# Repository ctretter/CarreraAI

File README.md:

# CarreraAI
Slot car racing ghost car using artificial intelligence algorithms

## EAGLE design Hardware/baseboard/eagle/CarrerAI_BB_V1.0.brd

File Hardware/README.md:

# Deprecated due to power supply issues

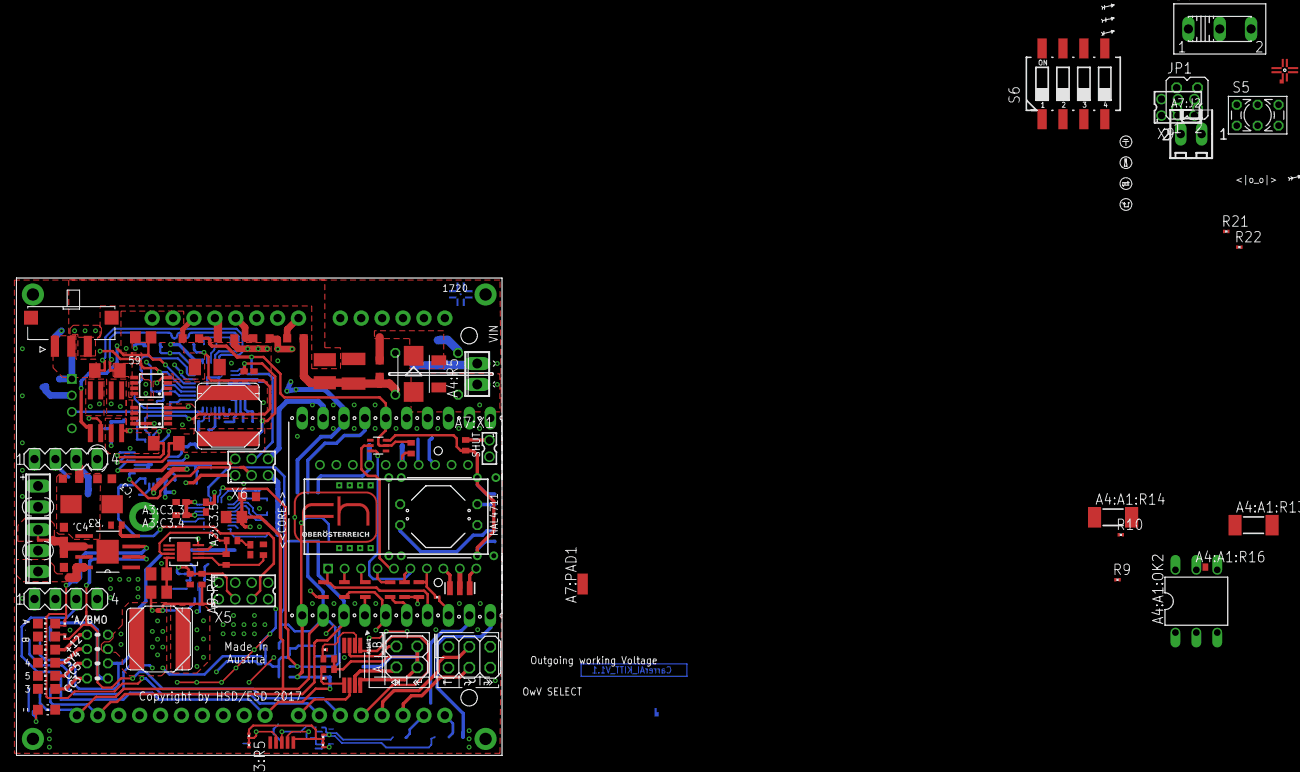
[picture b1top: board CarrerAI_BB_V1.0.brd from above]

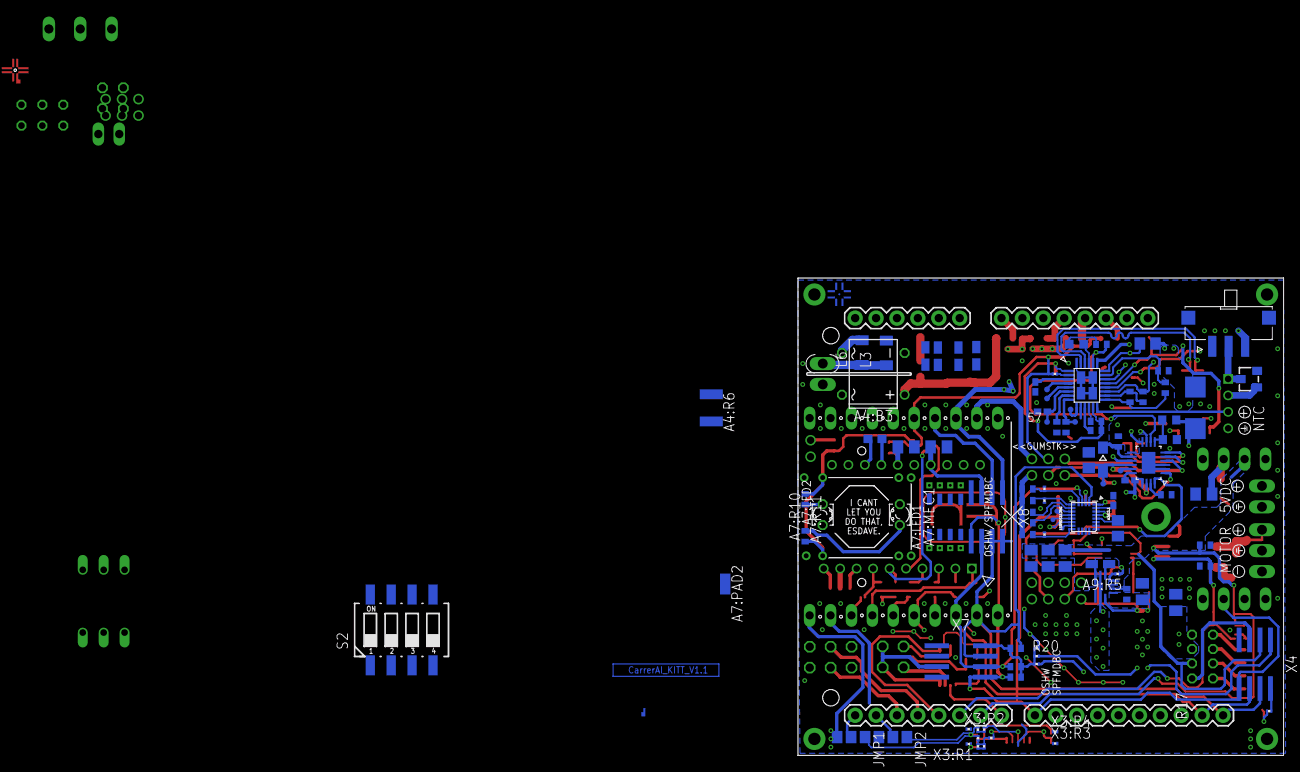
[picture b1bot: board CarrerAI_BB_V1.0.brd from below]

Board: 4 copper layers, 59.0 x 58.0 mm, 227 parts (102 on the bottom side), 139 nets.

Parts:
A2:C1: 4.7uF/25V; C0805K
A2:C2: 100nF/25V⇤; C0603K
A2:C3: 47uF/25V⇤; CT6032
A2:C4, A2:C5: 220nF/25V⇤; C0603
A2:L1, A4:L1: BEAD; L2012C
A2:R1, A2:R2: 10kR/⎑; R0402
A2:R3: 2k2R; R0402
A2:U1: DRV8871; HSOP8
A3:C3.1, A3:C3.XX: 10nF/⇤; C0805
A3:C3.2, A3:C3.3, A3:C3.4, A3:C3.5: 100nF/⇤; C0402K
A3:R3.1, A3:R3.2, A3:R3.5, A3:R3.6, A5:R11, A5:R12, A7:R9: 10kR/⎒; R0402
A3:R3.3, A3:R3.4, A3:R3.11: 10kR/⎑; R0201
A3:R3.9: 60R/⇤; R0603
A3:R3.10: 10k/⎒; R0402
A3:U3.1: LSM9DS1LONG; KITT.IC_LGA-24
A3:☇1, A3:☇2, A3:☇3: PTR1TP06R; TP06R
A4:A1:OK2: Si8710; DIL06
A4:A1:R13, A4:A1:R14: MINI_MELF-0207R
A4:A1:R16: R0402
A4:B3: DBDB102G; DB
A4:C1: 10uF; C1210K
A4:D1: SMB
A4:F1: 1.5A->750mA; R1210
A4:R1, A4:R3: 10kR; R0805W
A4:R2, A4:R4: 2.2kR; R0805W
A4:R5: VARISTORCN1206; CT/CN1206
A4:R6: VARISTORCN1210; CT/CN1210
A5:C1: 47nF/⇤; C0603K
A5:C2: 100uF/~5V; C1206K
A5:C4, A6:C5, A10:C1: 1uF/⇤; C0402K
A5:C5, A5:C6: 10nF/⇤; C0402K
A5:R1: 8.2mR/⚻; R1206-KELV
A5:R2: 16kR/⇤; R0402
A5:R3: 1MR; R0805
A5:R4: 270kR; R0402
A5:R5: 5mR; R0805
A5:R6: 100kR/1%; R0402
A5:R7: 27kR/1%; R0402
A5:R8: 68kR/1%; R0402
A5:R9, A5:R10: 1kR/⇤; R0402
A5:T1: IRF7328; SOIC8
A5:U1: LTC4000LTC4000EUFD-ARMIN; QFN-28_UFD-L_LONG
A5:☇1, A5:☇2, A5:☇3, A5:☇6, A5:☇7, A6:☇1, A6:☇5: PTR1TP07R; TP07R
A6:C1: 1nF/⇤; C0402
A6:C2: 4.7uF/⇤; C0805
A6:C3: 100nF/⇤; C0402
A6:C4: 100uF; C/6032-28R
A6:D1: 30VBD,0.2A; SOD323-W
A6:L1: 10uH; TAIYO-YUDEN.NRS8030T4R7MJGJ
A6:R1: 15mR/25mW⚻; R1206-KELV
A6:R2: 51kR/1%; R0603
A6:R3: 12kR/1%; R0603
A6:T1, A6:T2: XX; MSOP8
A6:U1: LTC3891QFN50P-LONG; QFN50P-LONG
A7:C1: 2.2uF/⇤; C1608
A7:C2, A7:C3: 100nF/⇤; C0805K
A7:DCL1, A7:DCL2: DCL.OSH'3MM-SLK'; DCL.LOGO-OSH.3MM
A7:J2: 22-27-2021-02; 6410-02
A7:LED1, A7:LED2: LZR181
A7:MEC1: MEC.HAL4711/OPTICS; MEC.HAL4711
A7:PAD1, A7:PAD2: SMD1,27-2,54
A7:R1, A7:R5, A7:R6: 10kR/⎒; MINI_MELF-0102R
A7:R2, A7:R3, A7:R4: 100R/⇤; MINI_MELF-0102R
A7:R7, A7:R10, A7:R11: 200R; R0402
A7:R8: 0R; R0201
A7:U1: ADNS-3080
A7:U2: SI1922EDH; SC70-6
A7:X1: 87758-0216
A7:Y1: 24MHz; RESON-SMD
A7:⌁1, A7:⌁2, A7:⌁3, A7:⌁4, A7:⌁5, A7:⌁6, A7:⌁7, A7:⌁8, A7:⌁9, A7:⌁10, A7:⌁11, A7:⌁12, A7:⌁13, A7:⌁14, A7:⌁15, A7:⌁16, A7:⌁17, A7:⌁18, A7:⌁19, A7:⌁20: SINGLEPAD40MIL-BREAK; PAD40MIL.BREAK
A9:C1: 10uF/⇤; C0805K
A9:C2, A9:C3, A9:C4: 22uF/⇤; C0805K
A9:C5: 100nF; C0805K
A9:L1: 1uH; TAIYO-YUDEN.NRS8030T4R7MJGJ
A9:R1: 10kR/⎒; R0805W
A9:R2: 0R/⎵; R0402
A9:R3: 1MR/⎵; R0402
A9:R4: ~10kR/⎵; R0402
A9:R5: R0201
A9:U1: TPS6123X5V-LONG; 9-VQFN-HR_LONG
A10:R1: 430R; R0402
A10:R2: 25kR; R0402
A10:R3, A10:R4: XXMR; M0805
A10:R7: 2.32MR; R0402
A10:REF2: REF.LOGO.UASUAS-GRADE; DCL.LOGO.FHOOE-6MM-S
A10:U1: LTC1540CDD-LONG; DFN-8_DD
A11:U1: 2NANDSOP8; SOP65P490X110-8N
AMO: MOTO; CHIP-LED0805
BMO: MOTO; CHIP-LED0805
D2: MMBZXAL; TO236
JMP1, JMP2: 0R-JUMPA; A0R-JMP
JP1: JP2Q
JP4: 2X02
L1, L2, L4, L5: BEAD/0R/⎵; L2012C
L3, L6: CM CHOKE; L3216C
LED1: VINS; CHIP-LED0805
LED2: DC3; CHIP-LED0805
LED3: DC5; CHIP-LED0805
LED4: SY4; CHIP-LED0805
LED5: PROBLEM; CHIP-LED0805
R1, R8, R15, R16: 100R; 0204V
R2, R6, R7, R9, R10, R11, R12, R18, R19, R20, R21, R22: R0201
R3, R4, R5, R13, R14: 10k/⎒; R0402
R17: 100R; R0201
REF1: REF.EDULIMIT; REF_EAGLE.EDULIMIT
S1, S3: SS312SAH4-R; SW_SS312SAH4-R
S2, S6: 219-04; CTS-219-04
S4: 255SB
S5: 9450-2
SV1, SV2: MA04-1
U$1: PASSER-CIRCLE
X1: JST-4POS-2X4POS; JST-PHR-4
X1.2: TACH/LAP; 2X03
X2: 3POL254
X2.2: VRAILS+; 2POL254
X2.3: SoC; 2POL254
X3:R1, X3:R2, X3:R3, X3:R4, X3:R5, X3:R21, X3:R22, X3:R23, X3:R24, X3:R25, X3:R26, X3:R27, X3:R28, X3:R29: R0201
X3:U$2: 1051330011; POS-5
X4: SYSTEMI-SW; SYSTEWI-BR1.SOIC8C
X5: 87758-0816
X6, X9: 87758-0616
X7: SYSTEMI-SE; SYSTEWI-BR1.SOIC8C
X8: STMI-CW/GPIO; SYSTEWI-BR1.SOIC16
XA1: ARDUINO_UNO; AU_PINS

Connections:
!CS0: A7:R1.2, A7:U1.1, A7:⌁14.P$1, XA1.IO.10
!CS1: A7:R8.2, A7:⌁13.P$1, XA1.IO.9
!RST: A5:U1.2, R2.2
+3V3: A3:C3.3.1, A3:C3.4.1, A3:C3.5.1, A3:R3.1.1, A3:R3.2.1, A3:R3.5.1, A3:R3.6.1, A3:R3.10.1, A3:U3.1.1, A3:U3.1.3, A3:U3.1.22, A3:U3.1.23, A7:C2.1, A7:C3.1, A7:LED1.A, A7:LED2.A, A7:R1.1, A7:R5.1, A7:R6.1, A7:R9.1, A7:U1.12, A7:U1.15, A7:U1.17, A7:X1.2, A7:⌁4.P$1, A11:U1.8, JP4.2, JP4.4, L2.1, R1.2, R6.2, R13.2, R14.2, X1.2.5, X1.2.6, X4.6, X6.5, X6.6, X7.6, X8.6
+4.1V: A5:R8.2, A5:T1.7, A5:T1.8, A5:U1.17, S1.3, SV2.1
+5V: A7:⌁5.P$1, A9:C2.1, A9:C3.1, A9:C4.1, A9:R1.2, A9:U1.6, A9:U1.9, L1.1, R7.2, R15.1, SV2.2, X2.3.2, X3:R23.2, X4.7, X5.2, X8.7
+18V: A2:C1.1, A2:L1.2, A4:B3.+, A4:C1.1, A4:F1.1, A4:L1.2, A4:R3.2, A4:R5.2, L4.1, R8.1, SV2.3
A2:ILIM: A2:R3.1, A2:U1.4
A2:VM: A2:C2.1, A2:C3.+, A2:C4.1, A2:L1.1, A2:U1.5
A3:CS_AG: A3:R3.1.2, A3:U3.1.7
A3:CS_M: A3:R3.2.2, A3:U3.1.8
A3:DEN_AG: A3:R3.10.2, A3:R3.11.1, A3:U3.1.13
A3:DRDY_M: A3:U3.1.9, A3:☇1.TP
A3:INT2_AG: A3:U3.1.12, A3:☇3.TP
A3:INT_M: A3:U3.1.10, A3:☇2.TP
A3:SDO_AG: A3:R3.3.1, A3:R3.6.2, A3:U3.1.5
A3:SDO_M: A3:R3.4.1, A3:R3.5.2, A3:U3.1.6
A3:↔C1: A3:C3.2.1, A3:U3.1.24
A3:↔CAP: A3:C3.1.1, A3:U3.1.21
A4:A1:GND: A4:A1:OK2.4, A4:A1:R14.1
A4:A1:N$1: A4:A1:OK2.5, A4:A1:R13.1, A4:A1:R16.2
A4:A1:N$2: A4:A1:OK2.2, A4:A1:R14.2
A4:A1:N$3: A4:A1:OK2.6, A4:A1:R16.1
A4:N$1: A4:D1.C, A4:L1.1, A4:R1.2
A5:BGATE: A5:T1.2, A5:U1.18
A5:BIAS: A5:C4.1, A5:R11.2, A5:R12.2, A5:U1.1, A5:U1.13
A5:CC: A5:C1.2, A5:U1.25
A5:CL: A5:R9.2, A5:U1.8, A5:☇6.TP
A5:CSN: A5:R5.1, A5:T1.1, A5:U1.19
A5:CX: A5:R10.2, A5:U1.7
A5:IBMON: A5:C6.1, A5:U1.6, A5:☇7.TP
A5:IGATE: A5:R3.2, A5:T1.4, A5:U1.22
A5:IIMON: A5:C5.1, A5:U1.3
A5:IL: A5:U1.4, A5:☇3.TP
A5:N$4: A5:C1.1, A5:R2.1
A5:N$8: A5:R7.1, A5:R8.1, A5:U1.16
A5:OFB: A5:R4.1, A5:R6.2, A5:U1.21
A5:TMR: A5:U1.9, A5:☇1.TP
A5:↔CLN: A5:R1.K+, A5:U1.26
A5:↔FBG: A5:R6.1, A5:R7.2, A5:U1.15
A5:↔IN: A5:R1.K-, A5:U1.27
A6:BG: A6:T2.4, A6:U1.13
A6:DDC.EXTVCC: A6:U1.15, A6:☇1.TP
A6:SW✳: A6:C3.2, A6:L1.2, A6:T1.1, A6:T1.2, A6:T1.3, A6:T2.5, A6:T2.6, A6:T2.7, A6:T2.8, A6:U1.11
A6:TG: A6:T1.4, A6:U1.10
A6:TRACK/SS: A6:C1.1, A6:U1.19
A6:~SENSE+: A6:L1.1, A6:R1.-
A6:↔BOOST: A6:C3.1, A6:D1.C, A6:U1.12
A6:↔ILIM: A6:C2.1, A6:D1.A, A6:U1.14, A6:U1.18, A6:☇5.TP
A6:↔SENSE+: A6:R1.K+, A6:U1.6
A6:↔SENSE-: A6:R1.K-, A6:U1.5
A6:↔VFB: A6:R2.2, A6:R3.1, A6:U1.7
A7:!PD: A7:R6.2, A7:R8.1, A7:U1.7
A7:LEDCTRL: A7:U1.5, A7:U2.2
A7:N$1: A7:LED2.K, A7:R11.2
A7:N$2: A7:LED1.K, A7:R10.2
A7:N$5: A7:C1.1, A7:U1.13
A7:N$6: A7:C1.2, A7:U1.14
A7:OD\!SHUT: A7:R7.1, A7:R10.1, A7:R11.1, A7:U2.6
A7:RST: A7:R5.2, A7:U1.6, A7:U2.3
A7:SHUT: A7:R7.2, A7:X1.1
A7:U1.GUARD: A7:U1.9, A7:Y1.2
A7:U1.MISO: A7:R2.2, A7:U1.2
A7:U1.MOSI: A7:R4.2, A7:U1.4
A7:U1.OSCIN✳: A7:U1.10, A7:Y1.1
A7:U1.OSCOUT✳: A7:U1.8, A7:Y1.3
A7:U1.SCLK: A7:R3.2, A7:U1.3
A9:CC: A9:C5.1, A9:R2.2, A9:U1.4
A9:✳SW: A9:L1.2, A9:U1.2
A10:COMP: A10:C1.1, A10:R1.1
A10:HYST: A10:R2.2, A10:R7.2, A10:U1.5
A10:IN+&REF: A10:R1.2, A10:R2.1, A10:U1.3, A10:U1.6
A10:IN-: A10:R3.2, A10:R4.1, A10:U1.4
AUX.USB/D+_P: JMP2.1, X3:R24.1
AUX.USB/D-_N: JMP1.1, X3:R25.1
DDC.CLN/VIN: A5:R1.+, A6:C5.1, A6:T1.5, A6:T1.6, A6:T1.7, A6:T1.8, A6:U1.17
GND: A2:C1.2, A2:C2.2, A2:C3.-, A2:C5.2, A2:R1.2, A2:R2.2, A2:R3.2, A2:U1.1, A2:U1.7, A2:U1.THERMAL, A3:C3.1.2, A3:C3.2.2, A3:C3.3.2, A3:C3.4.2, A3:C3.5.2, A3:C3.XX.2, A3:R3.3.2, A3:R3.4.2, A3:R3.9.2, A3:R3.11.2, A3:U3.1.14, A3:U3.1.15, A3:U3.1.16, A3:U3.1.17, A3:U3.1.18, A3:U3.1.19, A3:U3.1.20, A4:C1.2, A4:R2.1, A4:R4.1, A4:R5.1, A5:C2.2, A5:C4.2, A5:C5.2, A5:C6.2, A5:R9.1, A5:R10.1, A5:U1.10, A5:U1.28, A5:U1.EP-NE, A5:U1.EP-NW, A5:U1.EP-SE, A5:U1.EP-SW, A6:C1.2, A6:C2.2, A6:C4.-, A6:C5.2, A6:R3.2, A6:T2.1, A6:T2.2, A6:T2.3, A6:U1.2, A6:U1.3, A6:U1.16, A6:U1.21, A7:C2.2, A7:C3.2, A7:U1.16, A7:U1.19, A7:U2.1, A7:U2.4, A7:⌁1.P$1, A7:⌁10.P$1, A9:C1.2, A9:C2.2, A9:C3.2, A9:C4.2, A9:C5.2, A9:R2.1, A9:R3.1, A9:U1.1, A9:U1.5, A10:C1.2, A10:R3.1, A10:R7.1, A10:U1.1, A10:U1.2, A10:U1.EP, A11:U1.4, AMO.C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
ITH: A5:R2.2, A5:U1.24, A6:U1.8
LAP: X1.2.3, XA1.IO.2
MISO: A7:R2.1, A7:⌁16.P$1, XA1.IO.11
MOSI: A7:R4.1, A7:⌁15.P$1, XA1.IO.12
unnamed: A11:U1.3, JP4.1
unnamed: A11:U1.7, JP4.3
unnamed: LED1.A, R8.2
unnamed: L3.1, L6.1, X2.2.2
unnamed: A11:U1.2, R11.2, R13.1
unnamed: A11:U1.5, R12.2, R14.1
unnamed: LED2.A, R1.1
unnamed: LED3.A, R15.2
unnamed: A4:B3.AC1, L6.2
unnamed: LED4.A, R16.1
unnamed: LED5.A, R17.1
unnamed: R17.2, X4.1
unnamed: AMO.A, R18.1
unnamed: BMO.A, R19.1
PWR.MOTA: A2:R2.1, A2:U1.2, R19.2, XA1.IO.5
PWR.MOTB: A2:R1.1, A2:U1.3, R18.2, XA1.IO.6
SCLK: A7:R3.1, A7:⌁17.P$1, XA1.IO.13
SYSTWI.!INT: A3:C3.XX.1, A3:R3.9.1, A3:U3.1.11, A7:⌁20.P$1, R5.1, SV1.3, X4.4, X7.4, X8.4, XA1.IO.8
SYSTWI.SCL: A3:U3.1.2, A7:⌁19.P$1, R3.1, SV1.1, X4.2, X7.2, X8.2, XA1.SCL
SYSTWI.SDA: A3:U3.1.4, A7:⌁18.P$1, R4.1, SV1.2, X4.3, X7.3, X8.3, XA1.SDA
SYSTWI.VBUS: R3.2, R4.2, R5.2, R6.1, R7.1, R20.1, X7.1
TACH: X1.2.4, XA1.IO.3
TOP.5VEN: A9:R3.2, A9:R4.1, A9:R5.1, A9:R5.2, A9:U1.7, A10:U1.8, X5.3
TOP.!CHRG: A5:R11.1, A5:U1.12
TOP.!FLT: A5:R12.1, A5:U1.11
TOP.!RST: A7:R9.2, A7:U2.5, A7:⌁6.P$1, L5.1, R2.1, X6.4
TOP.BAT+NTC: A5:U1.14, X1.3
TOP.BAT/CON: D2.2, S1.2, X1.1
TOP.ENC: A5:U1.5, A5:☇2.TP
TOP.FREQ: A6:U1.20, X5.5
TOP.INACT: A9:R1.1, A9:U1.8
TOP.MODE: A6:U1.1, X6.3
TOP.MOT-: A2:U1.8, X2.1
TOP.MTXS: A7:PAD2.1, A7:⌁12.P$1, JMP2.3
TOP.MVPRW: A4:R3.1, A4:R4.2
TOP.ODA: A11:U1.1, XA1.IO.4
TOP.ODB: A11:U1.6, XA1.IO.7
TOP.OS1IS2: A5:T1.3, A5:U1.23, A6:C4.+, A6:R1.+, A6:R2.1
TOP.PGOOD: A6:U1.9, X6.1
TOP.RRX: A4:R1.1, A4:R2.2, A7:PAD1.1, A7:⌁11.P$1, JMP1.3
TOP.RUN: A6:U1.4, X6.2
UNO.3V3: L2.2, XA1.3.3V
UNO.5V: L1.2, XA1.5V
UNO.RESET: L5.2, XA1.RESET
UNO.RX: JMP1.2, XA1.IO.0
UNO.TX: JMP2.2, XA1.IO.1
UNO.VIN: L4.2, XA1.VIN
VCC/2: A4:B3.AC2, A4:D1.A, A7:⌁7.P$1, X2.2.1
VF+OUT/IPC: A4:F1.2, S3.3
VF+OUT/SWITCH: A5:R1.-, S3.1, S3.2
VSYS: A5:C2.1, A5:R3.1, A5:R4.2, A5:R5.2, A5:T1.5, A5:T1.6, A5:U1.20, A7:⌁3.P$1, A9:C1.1, A9:L1.1, A9:R4.2, A9:U1.3, A10:R4.2, A10:U1.7, R16.2, R20.2, X3:R29.2, X4.8, X5.1, X8.8
X3:B-ID: X3:R5.1, X3:R27.2, X3:U$2.4
X3:N$5: X3:R22.2, X3:R24.2
X3:N$6: X3:R21.2, X3:R25.2, X3:R26.2, X3:R28.2
X3:O>D+: X3:R22.1, X3:U$2.3
X3:O>D-: X3:R21.1, X3:U$2.2
X3:O>VBUS: X3:R23.1, X3:R27.1, X3:R29.1, X3:U$2.1
✳TOP.MOT+: A2:C4.2, A2:C5.1, A2:U1.6, X2.3

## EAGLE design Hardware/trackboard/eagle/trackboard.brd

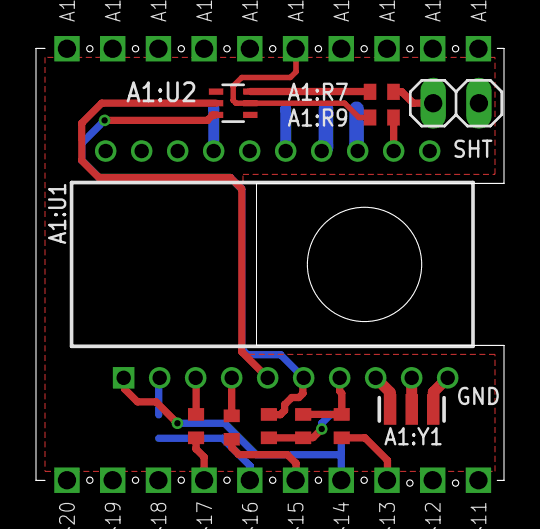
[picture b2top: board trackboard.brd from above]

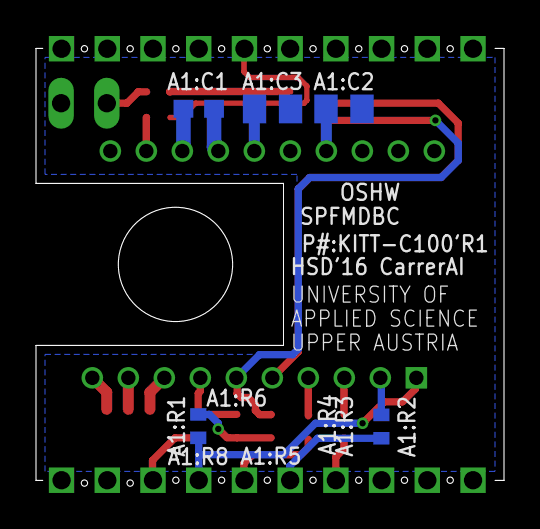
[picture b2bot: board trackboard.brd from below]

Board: 4 copper layers, 26.0 x 24.0 mm, 37 parts (6 on the bottom side), 21 nets.

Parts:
A1:C1: 2.2uF/⇤; C1608
A1:C2, A1:C3: 100nF/⇤; C0805K
A1:DCL2: DCL.OSH'3MM-SLK'; DCL.LOGO-OSH.3MM
A1:J1: 1X02
A1:R1, A1:R5, A1:R6, A1:R9: 10kR/⎒; R0402
A1:R2, A1:R3, A1:R4: 100R/⇤; R0402
A1:R7: 200R; R0402
A1:R8: 0R; R0402
A1:U1: ADNS-3080
A1:U2: SI1922EDH; SC70-6
A1:Y1: 24MHz; RESON-SMD
A1:⌁1, A1:⌁2, A1:⌁3, A1:⌁4, A1:⌁5, A1:⌁6, A1:⌁7, A1:⌁8, A1:⌁9, A1:⌁10, A1:⌁11, A1:⌁12, A1:⌁13, A1:⌁14, A1:⌁15, A1:⌁16, A1:⌁17, A1:⌁18, A1:⌁19, A1:⌁20: SINGLEPAD40MIL; PAD40MIL

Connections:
A1:!CS0: A1:R1.2, A1:U1.1, A1:⌁14.X
A1:!CS1: A1:R8.2, A1:⌁13.X
A1:!PD: A1:R6.2, A1:R8.1, A1:U1.7
A1:!RESET: A1:R9.2, A1:U2.5, A1:⌁6.X
A1:+3V3: A1:C2.1, A1:C3.1, A1:J1.1, A1:R1.1, A1:R5.1, A1:R6.1, A1:R9.1, A1:U1.12, A1:U1.15, A1:U1.17, A1:⌁4.X
A1:GND: A1:C2.2, A1:C3.2, A1:U1.16, A1:U1.19, A1:U2.1, A1:U2.4, A1:⌁1.X, A1:⌁10.X
A1:LEDCTRL: A1:U1.5, A1:U2.2
A1:MISO: A1:R2.1, A1:⌁16.X
A1:MOSI: A1:R4.1, A1:⌁15.X
A1:N$1: A1:R7.1, A1:U2.6
A1:N$5: A1:C1.1, A1:U1.13
A1:N$6: A1:C1.2, A1:U1.14
A1:N$8: A1:J1.2, A1:R7.2
A1:RST: A1:R5.2, A1:U1.6, A1:U2.3
A1:SCLK: A1:R3.1, A1:⌁17.X
A1:U1.GUARD: A1:U1.9, A1:Y1.2
A1:U1.MISO: A1:R2.2, A1:U1.2
A1:U1.MOSI: A1:R4.2, A1:U1.4
A1:U1.OSCIN✳: A1:U1.10, A1:Y1.1
A1:U1.OSCOUT✳: A1:U1.8, A1:Y1.3
A1:U1.SCLK: A1:R3.2, A1:U1.3

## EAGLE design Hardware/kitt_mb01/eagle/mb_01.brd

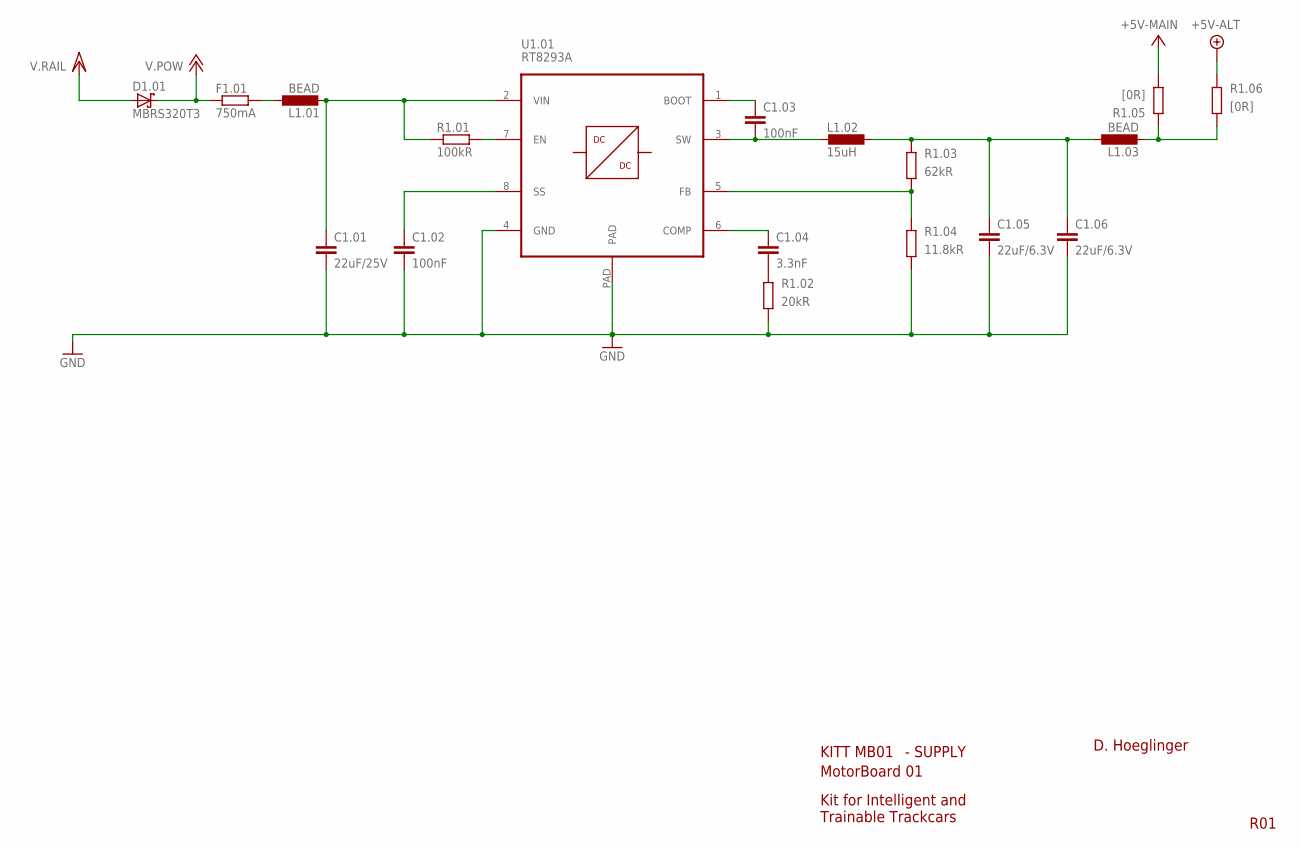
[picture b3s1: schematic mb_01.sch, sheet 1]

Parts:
C1.01: 22uF/25V; C1210K
C1.02, C1.03: 100nF; C0402K
C1.04: 3.3nF; C0402K
C1.05, C1.06: 22uF/6.3V; C1206K
D1.01: MBRS320T3; SMC
F1.01: 750mA; R1210
L1.01, L1.03: BEAD; L4516C
L1.02: 15uH; TAIYO-YUDEN.NRS8030T4R7MJGJ
R1.01: 100kR; R0402
R1.02: 20kR; R0402
R1.03: 62kR; R0402
R1.04: 11.8kR; R0402
R1.05, R1.06: [0R]; R0402
U1.01: RT8293A; SOIC-8-PAD

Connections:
+5V: R1.05.1, R1.06.2; also elsewhere on the board
+12V: D1.01.C, F1.01.1; also elsewhere on the board
GND: C1.01.2, C1.02.2, C1.05.2, C1.06.2, R1.02.1, R1.04.1, U1.01.4 (GND), U1.01.PAD; also elsewhere on the board
unnamed: F1.01.2, L1.01.1
unnamed: C1.01.1, L1.01.2, R1.01.1, U1.01.2 (VIN)
unnamed: R1.01.2, U1.01.7 (EN)
unnamed: C1.02.1, U1.01.8 (SS)
unnamed: C1.04.2, R1.02.2
unnamed: C1.04.1, U1.01.6 (COMP)
unnamed: R1.03.1, R1.04.2, U1.01.5 (FB)
unnamed: C1.05.1, C1.06.1, L1.02.1, L1.03.1, R1.03.2
unnamed: C1.03.2, L1.02.2, U1.01.3 (SW)
unnamed: C1.03.1, U1.01.1 (BOOT)
unnamed: L1.03.2, R1.05.2, R1.06.1
VCC/2: D1.01.A; also elsewhere on the board

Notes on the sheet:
KITT MB01
Kit for Intelligent and Trainable Trackcars
MotorBoard 01
- SUPPLY
D. Hoeglinger
R01

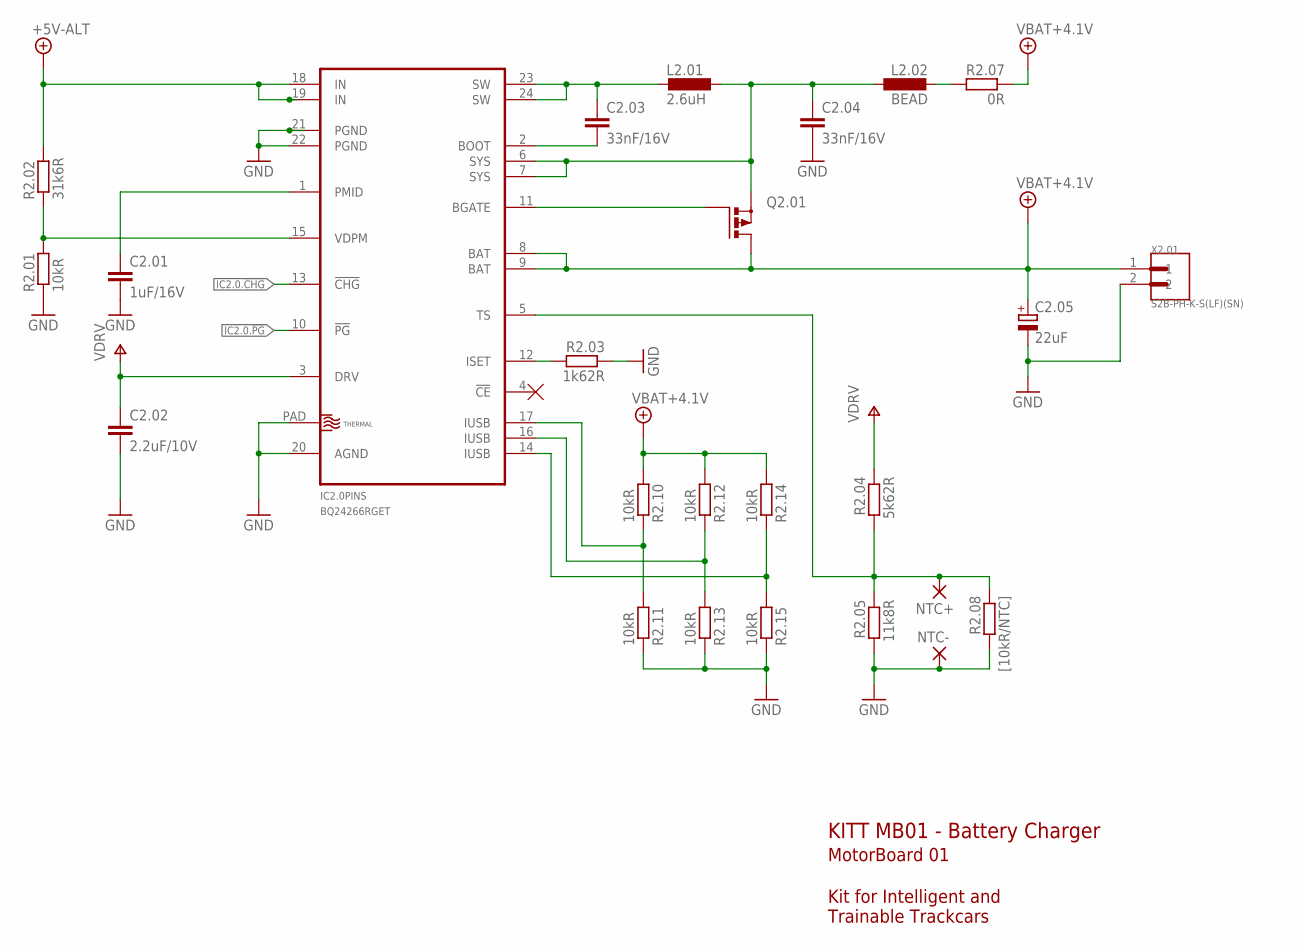
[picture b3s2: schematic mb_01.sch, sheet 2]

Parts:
C2.01: 1uF/16V; C0805
C2.02: 2.2uF/10V; C0603K
C2.03: 33nF/16V; C0603
C2.04: 33nF/16V; C0805
C2.05: 22uF; A/3216-18R
IC2.0: BQ24266RGET; VQFN-24
L2.01: 2.6uH; TAIYO-YUDEN.NRS8030T4R7MJGJ
L2.02: BEAD; L4516C
NTC+: SMD2; SMD1,27-2,54
NTC-: SMD2; SMD1,27-2,54
Q2.01: P-MOSFET-SO8; SO-08
R2.01, R2.10, R2.11, R2.12, R2.13, R2.14, R2.15: 10kR; R0402
R2.02: 31k6R; R0402
R2.03: 1k62R; R0402
R2.04: 5k62R; R0402
R2.05: 11k8R; R0402
R2.07: 0R; R0402
R2.08: [10kR/NTC]; R0402
X2.01: S2B-PH-K-S(LF)(SN); JST_S2B-PH-K-S(LF)(SN)

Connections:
+4.1V: C2.05.+, IC2.0.8 (BAT), IC2.0.9 (BAT), Q2.01.5 (D), Q2.01.6 (D), Q2.01.7 (D), Q2.01.8 (D), R2.07.1, R2.10.2, R2.12.2, R2.14.2, X2.01.1; also elsewhere on the board
+5V: IC2.0.18 (IN), IC2.0.19 (IN), R2.02.2; also elsewhere on the board
GND: C2.01.2, C2.02.2, C2.04.2, C2.05.-, IC2.0.20 (AGND), IC2.0.21 (PGND), IC2.0.22 (PGND), IC2.0.PAD (THERMAL), NTC-.1, R2.01.1, R2.03.1, R2.05.2, R2.08.2, R2.11.1, R2.13.1, R2.15.1, X2.01.2; also elsewhere on the board
unnamed 30: IC2.0.15 (VDPM), R2.01.2, R2.02.1; also elsewhere on the board
unnamed: L2.02.2, R2.07.2
unnamed 33: IC2.0.12 (ISET), R2.03.2; also elsewhere on the board
unnamed 34: IC2.0.17 (IUSB), R2.10.1, R2.11.2; also elsewhere on the board
unnamed 35: IC2.0.16 (IUSB), R2.12.1, R2.13.2; also elsewhere on the board
unnamed 36: IC2.0.14 (IUSB), R2.14.1, R2.15.2; also elsewhere on the board
U2.0/BGATE: IC2.0.11 (BGATE), Q2.01.4 (G); also elsewhere on the board
U2.0/BOOT: C2.03.2, IC2.0.2 (BOOT); also elsewhere on the board
U2.0/DRV: C2.02.1, IC2.0.3 (DRV), R2.04.1; also elsewhere on the board
U2.0/PMID: C2.01.1, IC2.0.1 (PMID); also elsewhere on the board
U2.0/SW: C2.03.1, IC2.0.23 (SW), IC2.0.24 (SW), L2.01.2; also elsewhere on the board
U2.0/SYS: C2.04.1, IC2.0.6 (SYS), IC2.0.7 (SYS), L2.01.1, L2.02.1, Q2.01.1 (S), Q2.01.2 (S), Q2.01.3 (S); also elsewhere on the board
U2.0/TS: IC2.0.5 (TS), NTC+.1, R2.04.2, R2.05.1, R2.08.1; also elsewhere on the board

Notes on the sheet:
KITT MB01 - Battery Charger
Kit for Intelligent and Trainable Trackcars
MotorBoard 01

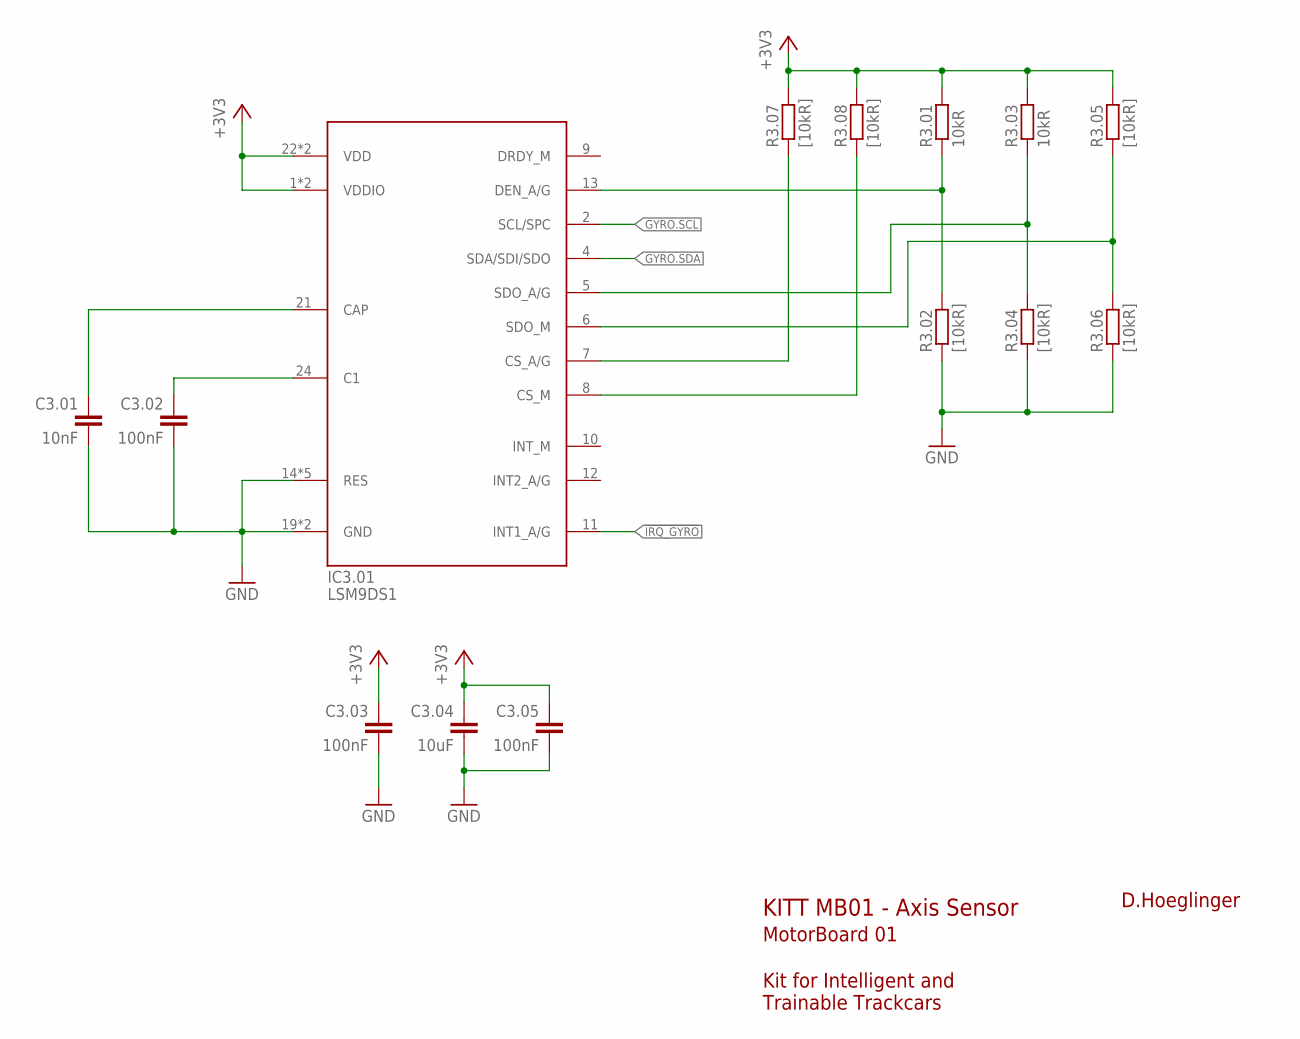
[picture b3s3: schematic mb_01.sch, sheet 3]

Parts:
C3.01: 10nF; C0603
C3.02, C3.03, C3.05: 100nF; C0402
C3.04: 10uF; C0603K
IC3.01: LSM9DS1; LGA-24
R3.01, R3.03: 10kR; R0402
R3.02, R3.04, R3.05, R3.06, R3.07, R3.08: [10kR]; R0402

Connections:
!IRQ_GYRO: IC3.01.11 (INT1_A/G); also elsewhere on the board
+3V3: C3.03.1, C3.04.1, C3.05.1, IC3.01.1 (VDDIO), IC3.01.3 (VDDIO), IC3.01.22 (VDD), IC3.01.23 (VDD), R3.01.2, R3.03.2, R3.05.2, R3.07.2, R3.08.2; also elsewhere on the board
GND: C3.01.2, C3.02.2, C3.03.2, C3.04.2, C3.05.2, IC3.01.14 (RES), IC3.01.15 (RES), IC3.01.16 (RES), IC3.01.17 (RES), IC3.01.18 (RES), IC3.01.19 (GND), IC3.01.20 (GND), R3.02.1, R3.04.1, R3.06.1; also elsewhere on the board
GYRO.SCL: IC3.01.2 (SCL/SPC); also elsewhere on the board
GYRO.SDA: IC3.01.4 (SDA/SDI/SDO); also elsewhere on the board
unnamed: C3.01.1, IC3.01.21 (CAP)
unnamed: C3.02.1, IC3.01.24 (C1)
unnamed: IC3.01.13 (DEN_A/G), R3.01.1, R3.02.2
unnamed: IC3.01.5 (SDO_A/G), R3.03.1, R3.04.2
unnamed: IC3.01.7 (CS_A/G), R3.07.1
unnamed: IC3.01.6 (SDO_M), R3.05.1, R3.06.2
unnamed: IC3.01.8 (CS_M), R3.08.1

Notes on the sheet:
KITT MB01 - Axis Sensor
Kit for Intelligent and Trainable Trackcars
MotorBoard 01
D.Hoeglinger

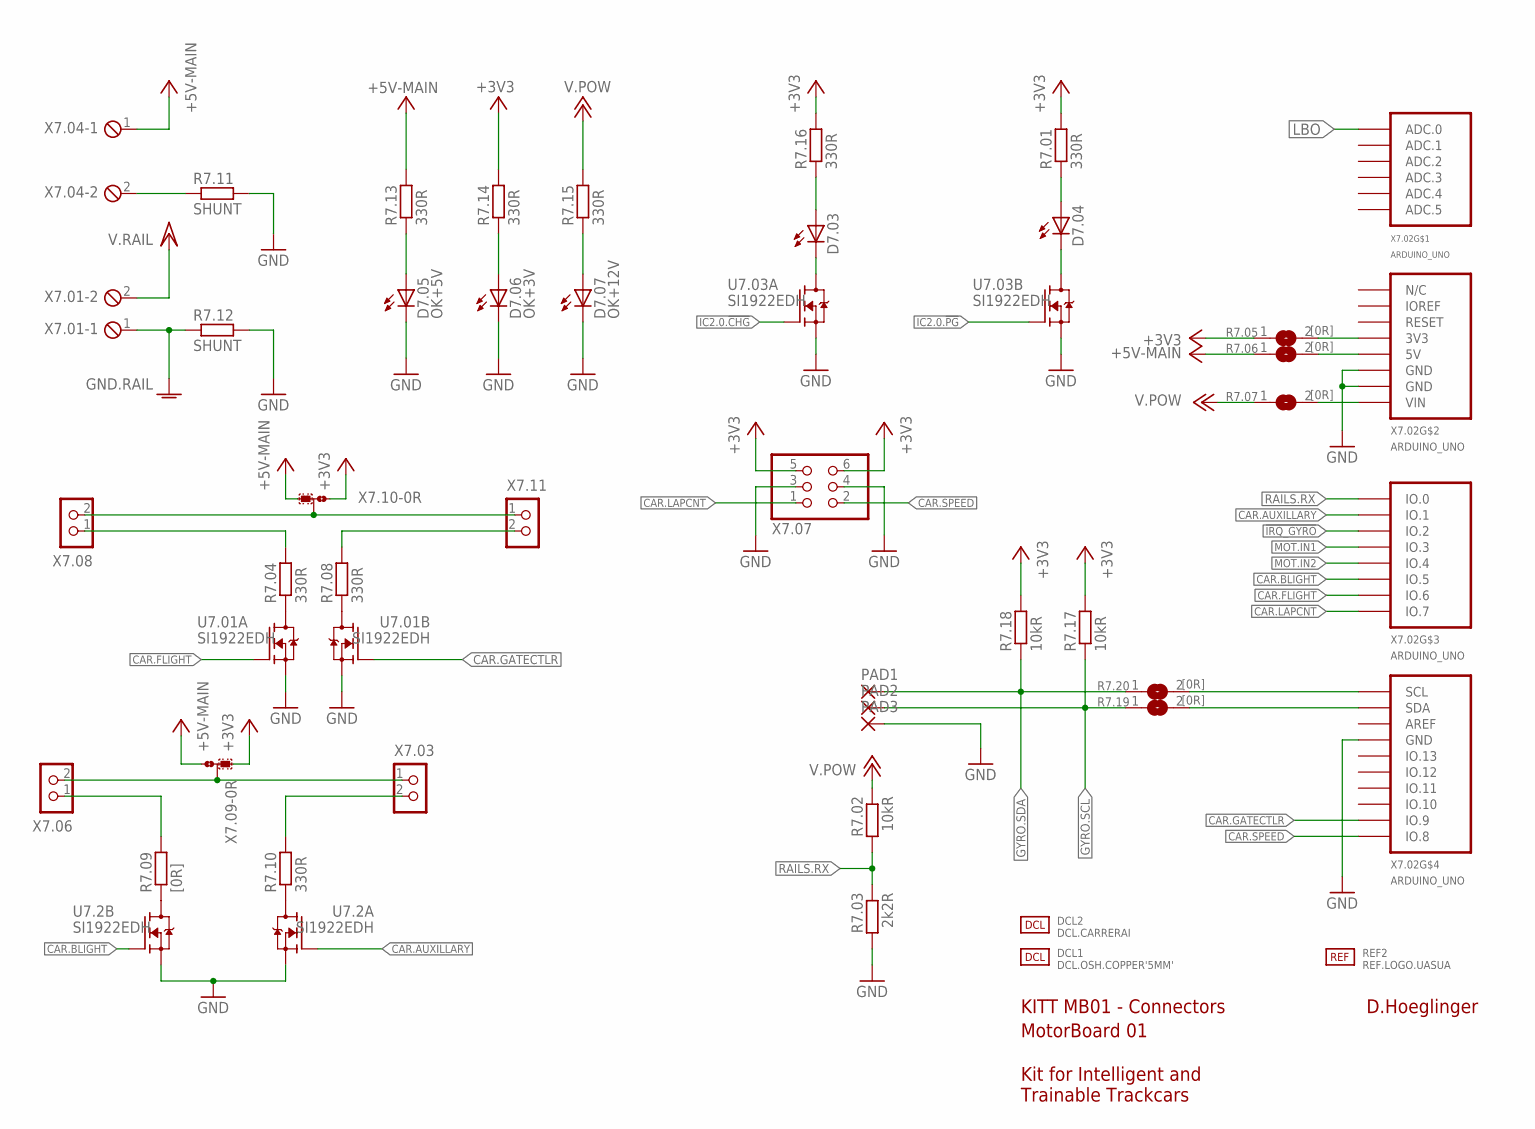
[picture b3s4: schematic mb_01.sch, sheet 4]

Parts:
D7.03, D7.04: LEDCHIPLED_1206; CHIPLED_1206
D7.05: OK+5V; CHIPLED_1206
D7.06: OK+3V; CHIPLED_1206
D7.07: OK+12V; CHIPLED_1206
DCL1: DCL.OSH.COPPER'5MM'; DCL.LOGO-OSH.5MM
DCL2: DCL.CARRERAI; DCL.LOGO-CARRERAI.W30MM
PAD1, PAD2, PAD3: SMD2; SMD1,27-2,54
R7.01, R7.04, R7.08, R7.10, R7.13, R7.14, R7.15, R7.16: 330R; R0603
R7.02: 10kR; M0805
R7.03: 2k2R; M0805
R7.05, R7.06, R7.07, R7.19, R7.20: [0R]; SJ
R7.09: [0R]; R0603
R7.11, R7.12: SHUNT; R1206
R7.17, R7.18: 10kR; R0402
REF2: REF.LOGO.UASUA; REF_LOGO_UASUA
U7.01, U7.2, U7.03: SI1922EDH; SC70-6
X7.01, X7.04: MPT2; 2POL254
X7.02: ARDUINO_UNO; AU_PINS
X7.03, X7.06, X7.08, X7.11: CON_HEADER_1X02; M1X2_MALE_RIGHT_ANGLED_SMD
X7.07: PINHD-2X3/90; 2X03/90
X7.09, X7.10: 0R-JUMPA; A0R-JMP

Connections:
!IRQ_GYRO: X7.02.IO.2; also elsewhere on the board
+3V3: R7.01.2, R7.05.1, R7.14.2, R7.16.2, R7.17.2, R7.18.2, X7.07.5, X7.07.6, X7.09.1, X7.10.1; also elsewhere on the board
+5V: R7.06.1, R7.13.2, X7.04.1, X7.09.3, X7.10.3; also elsewhere on the board
+12V: R7.02.1, R7.07.1, R7.15.2; also elsewhere on the board
CAR.AUXILLARY: U7.2.2 (G), X7.02.IO.1
CAR.BLIGHT: U7.2.5 (G), X7.02.IO.5
CAR.FLIGHT: U7.01.2 (G), X7.02.IO.6
CAR.GATECTLR: U7.01.5 (G), X7.02.IO.9
CAR.LAPCNT: X7.02.IO.7, X7.07.1
CAR.SPEED: X7.02.IO.8, X7.07.2
GND: D7.05.C, D7.06.C, D7.07.C, PAD3.1, R7.03.2, R7.11.2, R7.12.2, U7.01.1 (S), U7.01.4 (S), U7.2.1 (S), U7.2.4 (S), U7.03.1 (S), U7.03.4 (S), X7.02.GND2 (GND), X7.02.GND3 (GND), X7.02.GND.1 (GND), X7.07.3, X7.07.4; also elsewhere on the board
GNDA: R7.12.1, X7.01.1
GYRO.SCL: PAD2.1, R7.17.1, R7.19.1; also elsewhere on the board
GYRO.SDA: PAD1.1, R7.18.1, R7.20.1; also elsewhere on the board
IC2.0.!CHG: U7.03.2 (G); also elsewhere on the board
IC2.0.!PG: U7.03.5 (G); also elsewhere on the board
LBO: X7.02.ADC.0; also elsewhere on the board
MOT.IN1: X7.02.IO.3; also elsewhere on the board
MOT.IN2: X7.02.IO.4; also elsewhere on the board
unnamed: R7.04.1, U7.01.6 (D)
unnamed: R7.05.2, X7.02.3.3V (3V3)
unnamed: R7.06.2, X7.02.5V
unnamed: R7.07.2, X7.02.VIN
unnamed: R7.08.1, U7.01.3 (D)
unnamed: R7.11.1, X7.04.2
unnamed: D7.03.C, U7.03.6 (D)
unnamed: D7.03.A, R7.16.1
unnamed: D7.04.A, R7.01.1
unnamed: D7.04.C, U7.03.3 (D)
unnamed: D7.05.A, R7.13.1
unnamed: D7.06.A, R7.14.1
unnamed: R7.04.2, X7.08.1
unnamed: D7.07.A, R7.15.1
unnamed: X7.08.2, X7.10.2, X7.11.1
unnamed: R7.09.2, X7.06.1
unnamed: R7.09.1, U7.2.3 (D)
unnamed: X7.03.1, X7.06.2, X7.09.2
unnamed: R7.19.2, X7.02.SDA
unnamed: R7.08.2, X7.11.2
unnamed: R7.10.1, U7.2.6 (D)
unnamed: R7.10.2, X7.03.2
unnamed: R7.20.2, X7.02.SCL
RAILS.RX: R7.02.2, R7.03.1, X7.02.IO.0
VCC/2: X7.01.2; also elsewhere on the board

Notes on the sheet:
D.Hoeglinger
KITT MB01 - Connectors
MotorBoard 01
Kit for Intelligent and Trainable Trackcars

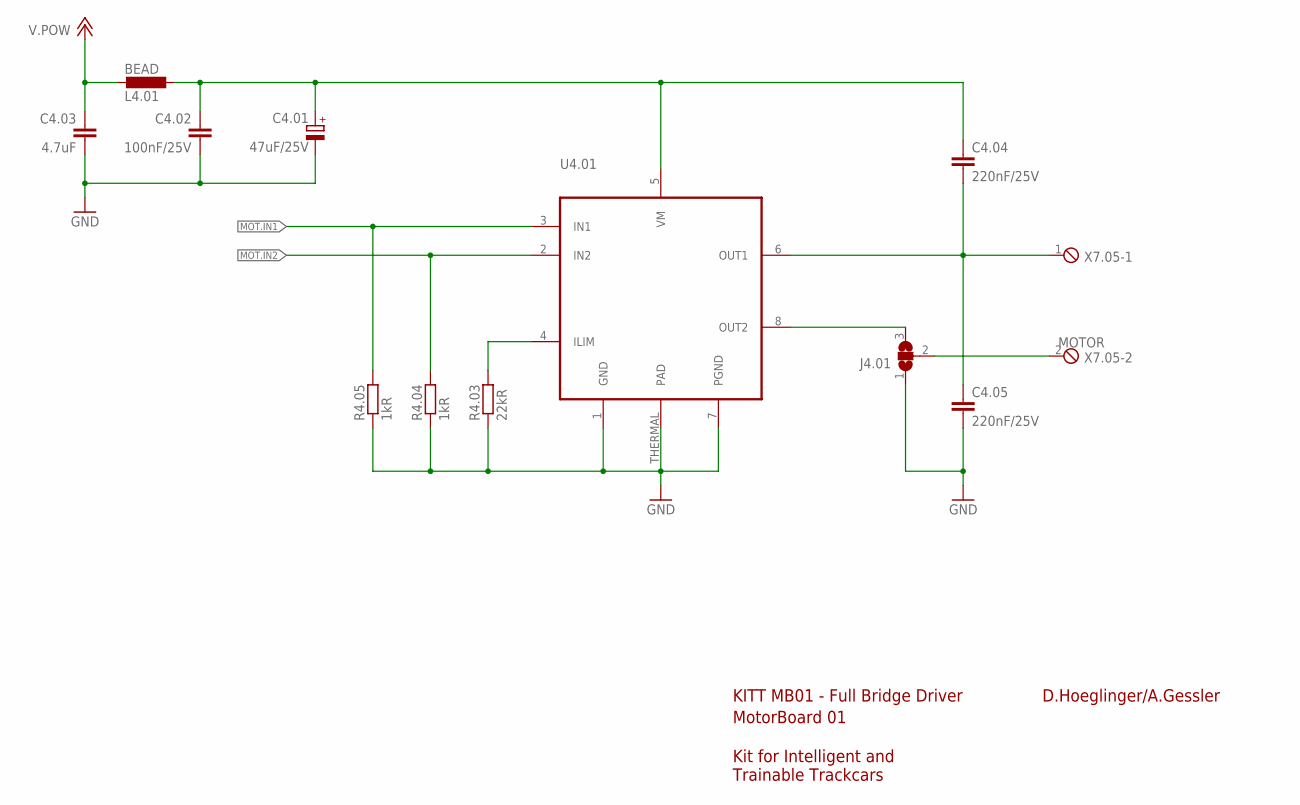
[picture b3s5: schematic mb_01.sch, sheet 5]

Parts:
C4.01: 47uF/25V; C/6032-28R
C4.02: 100nF/25V; C0603K
C4.03: 4.7uF; C0805K
C4.04, C4.05: 220nF/25V; C0603K
J4.01: SJ2W; SJ_2
L4.01: BEAD; L4516C
R4.03: 22kR; R0402
R4.04, R4.05: 1kR; R0402
U4.01: DRV8871; HSOP8
X7.05: MOTOR; 2POL254

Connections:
+12V: C4.03.1, L4.01.2; also elsewhere on the board
GND: C4.01.-, C4.02.2, C4.03.2, C4.05.2, J4.01.1, R4.03.1, R4.04.1, R4.05.1, U4.01.1 (GND), U4.01.7 (PGND), U4.01.THERMAL (PAD); also elsewhere on the board
MOT.IN1: R4.05.2, U4.01.3 (IN1); also elsewhere on the board
MOT.IN2: R4.04.2, U4.01.2 (IN2); also elsewhere on the board
unnamed: J4.01.2, X7.05.2
unnamed: C4.01.+, C4.02.1, C4.04.1, L4.01.1, U4.01.5 (VM)
unnamed: C4.04.2, C4.05.1, U4.01.6 (OUT1), X7.05.1
unnamed: J4.01.3, U4.01.8 (OUT2)
unnamed: R4.03.2, U4.01.4 (ILIM)

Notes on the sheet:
D.Hoeglinger/A.Gessler
KITT MB01 - Full Bridge Driver
Kit for Intelligent and Trainable Trackcars
MotorBoard 01

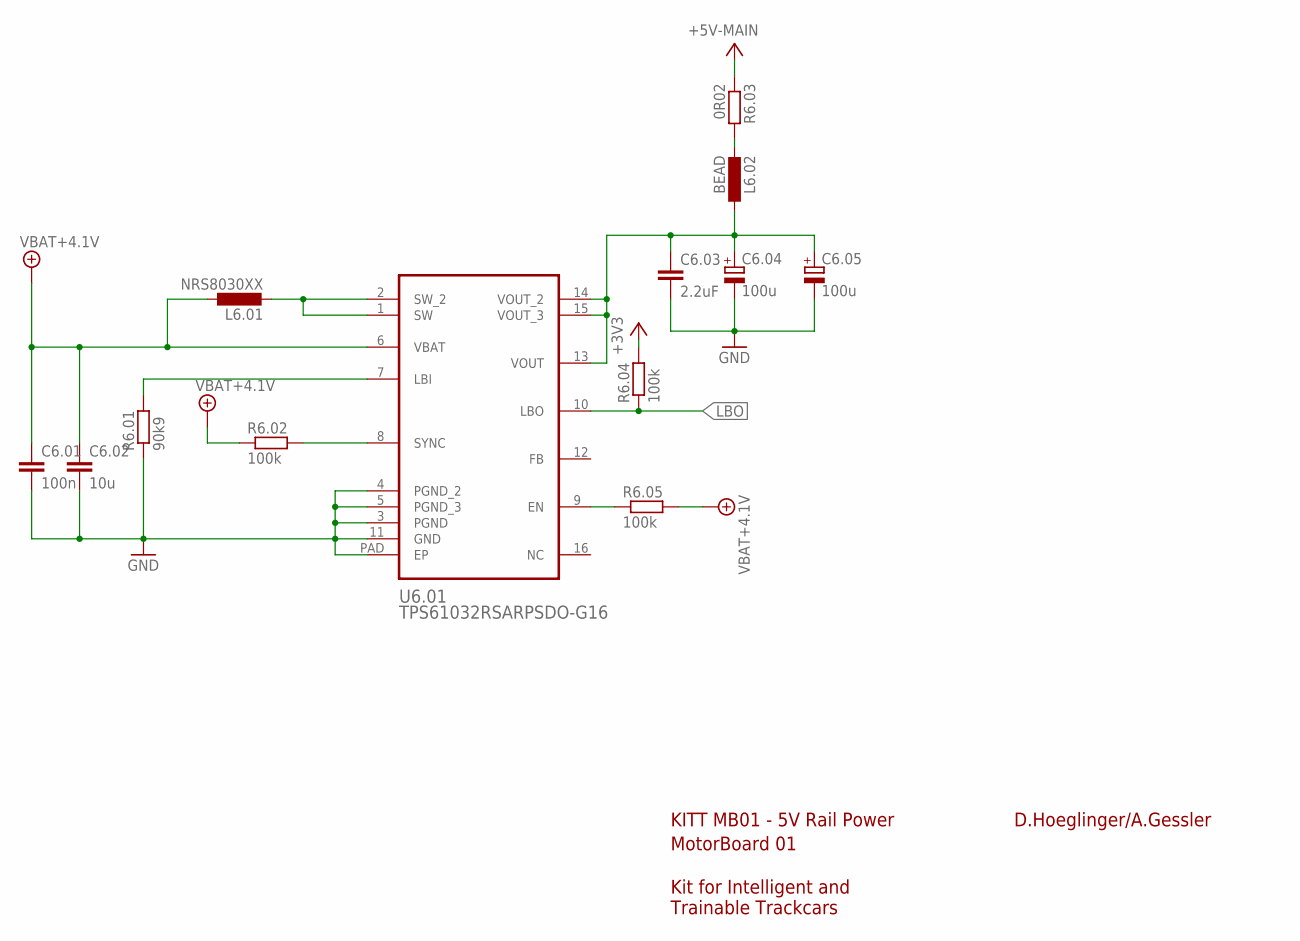
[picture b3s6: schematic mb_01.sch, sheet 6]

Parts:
C6.01: 100n; C0402
C6.02: 10u; C0603
C6.03: 2.2uF; C0603
C6.04, C6.05: 100u; C-2312
L6.01: NRS8030XX; TAIYO-YUDEN.NRS8030T4R7MJGJ
L6.02: BEAD; L4516C
R6.01: 90k9; R0402
R6.02, R6.04, R6.05: 100k; R0402
R6.03: 0R02; R0805
U6.01: TPS61032RSARPSDO-G16; R-PDSO-G16

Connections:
+3V3: R6.04.2; also elsewhere on the board
+4.1V: C6.01.1, C6.02.1, L6.01.1, R6.02.1, R6.05.2, U6.01.6 (VBAT); also elsewhere on the board
+5V: R6.03.1; also elsewhere on the board
GND: C6.01.2, C6.02.2, C6.03.2, C6.04.N (-), C6.05.N (-), R6.01.1, U6.01.3 (PGND), U6.01.4 (PGND_2), U6.01.5 (PGND_3), U6.01.11 (GND), U6.01.PAD (EP); also elsewhere on the board
LBO: R6.04.1, U6.01.10 (LBO); also elsewhere on the board
unnamed: L6.02.2, R6.03.2
unnamed: R6.05.1, U6.01.9 (EN)
unnamed: L6.01.2, U6.01.1 (SW), U6.01.2 (SW_2)
unnamed: R6.01.2, U6.01.7 (LBI)
unnamed: R6.02.2, U6.01.8 (SYNC)
unnamed: C6.03.1, C6.04.P (+), C6.05.P (+), L6.02.1, U6.01.13 (VOUT), U6.01.14 (VOUT_2), U6.01.15 (VOUT_3)

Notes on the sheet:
D.Hoeglinger/A.Gessler
KITT MB01 - 5V Rail Power
Kit for Intelligent and Trainable Trackcars
MotorBoard 01

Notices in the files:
Hardware/baseboard/eagle/CarrerAI_BB_V1.0.brd:
Die Schriftzüge "Made in Austria" & "Copyright by HSD/ESD 2017" auf der Platine platzieren.
